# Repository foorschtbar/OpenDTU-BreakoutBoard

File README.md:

# openDTU Breakout Board

To read Hoymiles inverters there is a nice project called [openDTU](https://github.com/tbnobody/OpenDTU) which uses an ESP32 to talk to them. This is a PCB for a ESP32 (38 Pin) and a NRF24L01+PA+LNA radio module.

### PCB Ordering

:point_up: I still have a few PCBs left. If you are interested please contact me. Contact details can be found here: https://github.com/foorschtbar or visit my Tindie store:

## Case

You find the case on Printables: [Case for openDTU/ahoy Breakout Board (ESP32 and NRF24L01)](https://www.printables.com/model/421083-case-for-opendtuahoy-breakout-board-esp32-and-nrf2)

## Credits

This is a updated version. The original is from [dokuhn/openDTU-BreakoutBoard](https://github.com/dokuhn/openDTU-BreakoutBoard).

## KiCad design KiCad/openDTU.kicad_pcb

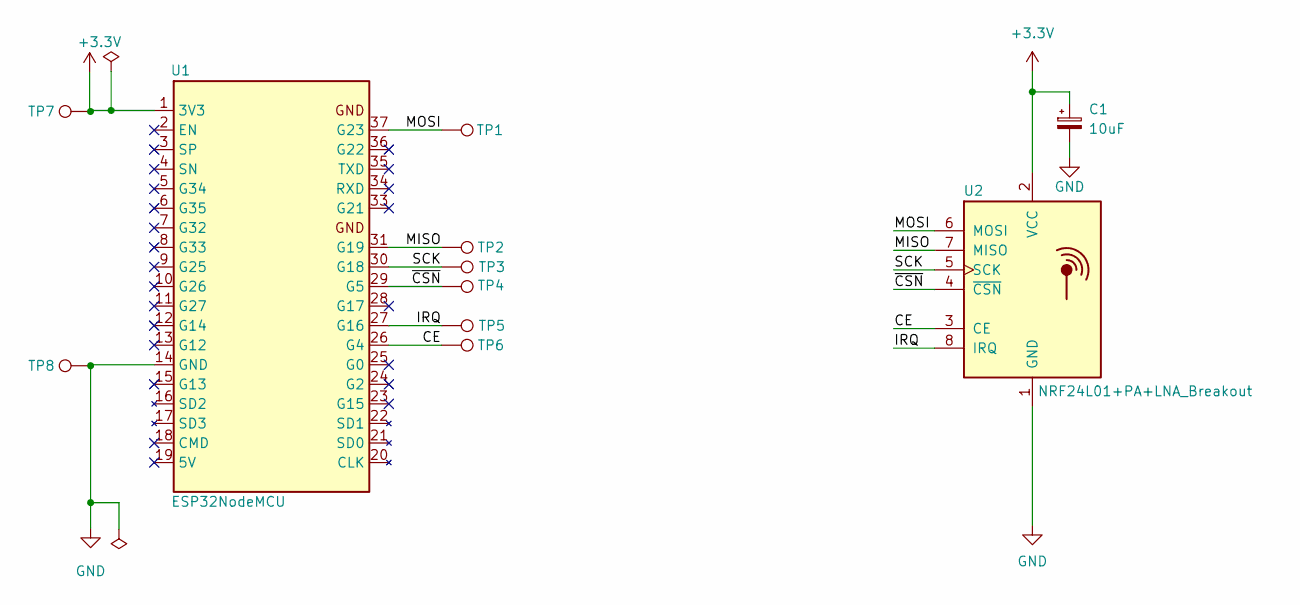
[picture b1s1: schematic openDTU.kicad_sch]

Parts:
C1: 10uF; CP_Radial_D5.0mm_P2.50mm
TP1, TP2, TP3, TP4, TP5, TP6, TP7, TP8: TestPoint; TestPoint_THTPad_D1.5mm_Drill0.7mm
U1: ESP32NodeMCU; ESP32-NodeMCU_WROOM_32
U2: NRF24L01+PA+LNA_Breakout; nRF24L01+PA+LNA_Breakout

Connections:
+3.3V: C1.1, TP7.1, U1.1 (3V3), U2.2 (VCC)
/CE: TP6.1, U1.26 (G4), U2.3 (CE)
/IRQ: TP5.1, U1.27 (G16), U2.8 (IRQ)
/MISO: TP2.1, U1.31 (G19), U2.7 (MISO)
/MOSI: TP1.1, U1.37 (G23), U2.6 (MOSI)
/SCK: TP3.1, U1.30 (G18), U2.5 (SCK)
/~CSN: TP4.1, U1.29 (G5), U2.4 (~CSN)
GND: C1.2, TP8.1, U1.14 (GND), U1.32 (GND), U1.38 (GND), U2.1 (GND)

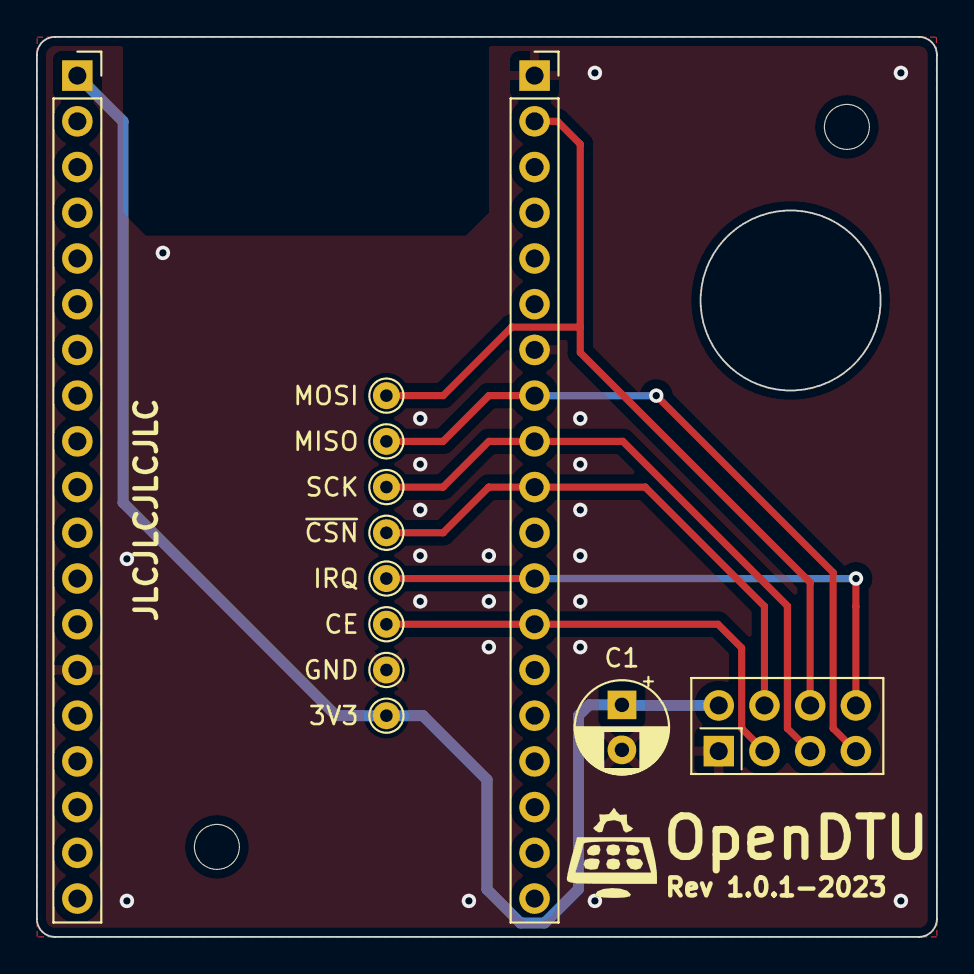
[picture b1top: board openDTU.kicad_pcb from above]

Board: 2 copper layers, 50.0 x 50.0 mm, 11 parts (0 on the bottom side), 8 nets.

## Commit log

2023-01-15 Added mounting holes and some other improvments
2023-01-16 Added mounting holes
2023-01-16 Project cleanup
2023-02-17 Updated to REV2.1
2023-02-18 Restructure folder
2023-02-18 Updated .gitignore
2023-02-18 Fixed typo
2023-03-11 Added 3D Model
2023-03-11 Updated Board to REV2.1
2024-04-20 Added Tindie store link
